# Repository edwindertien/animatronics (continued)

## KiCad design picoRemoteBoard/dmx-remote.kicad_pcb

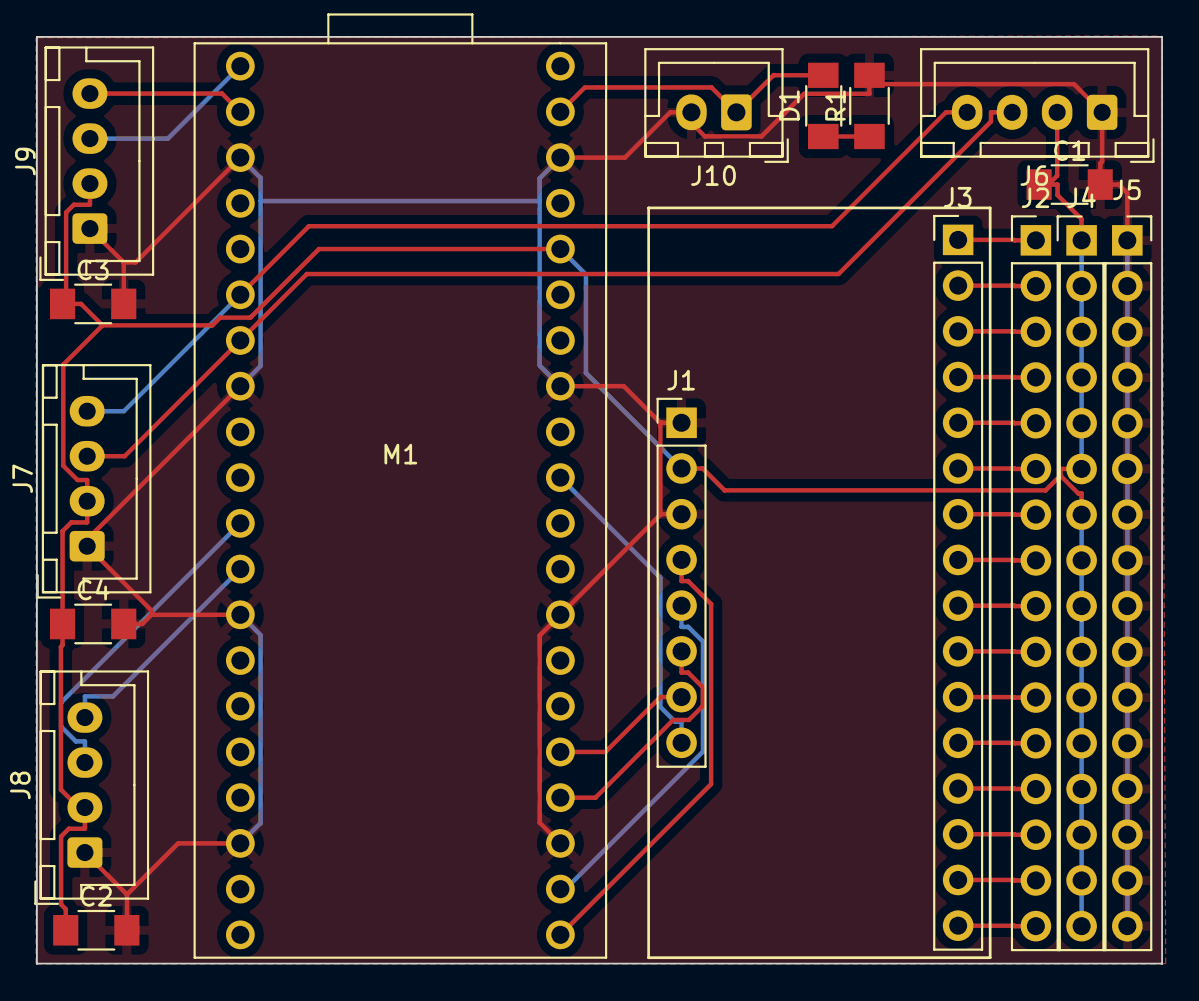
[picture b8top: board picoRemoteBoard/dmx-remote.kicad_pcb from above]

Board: 2 copper layers, 62.5 x 51.5 mm, 17 parts (0 on the bottom side), 31 nets.

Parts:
C1, C2, C3, C4: 100n; C_1206
D1: LED; LED_1206
J1: multiplexer control; PinHeader_1x08_P2.54mm_Vertical
J2: multiplexer in; PinHeader_1x16_P2.54mm_Vertical
J3: inputs; PinHeader_1x16_P2.54mm_Vertical
J4: vcc inputs; PinHeader_1x16_P2.54mm_Vertical
J5: gnd inputs; PinSocket_1x16_P2.54mm_Vertical
J6: oled; JST_XH_B4B-XH-A_1x04_P2.50mm_Vertical
J7: nunchuck; JST_XH_B4B-XH-A_1x04_P2.50mm_Vertical
J8: RF; JST_XH_B4B-XH-A_1x04_P2.50mm_Vertical
J9: DMX; JST_XH_B4B-XH-A_1x04_P2.50mm_Vertical
J10: power; JST_XH_B2B-XH-A_1x02_P2.50mm_Vertical
M1: Module_RaspberryPi_PicoW_Combined; RaspberryPi_PicoW_SocketTHT
R1: 330R; R_1206

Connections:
+3.3V: C1.1, C2.1, C3.1, C4.1, J1.2, J4.1, J4.2, J4.3, J4.4, J4.5, J4.6, J4.7, J4.8, J4.9, J4.10, J4.11, J4.12, J4.13, J4.14, J4.15, J4.16, J6.2, J7.2, J8.2, J9.2, M1.36 (3V3_OUT)
+5V: D1.2 (A), J10.1, M1.39 (VSYS)
/DMX-RxD: J9.3, M1.1 (GP0)
/DMX-TxD: J9.4, M1.2 (GP1)
/RF-RxD: J8.3, M1.11 (GP8)
/RF-TxD: J8.4, M1.12 (GP9)
/SCL: J6.3, J7.3, M1.7 (GP5)
/SDA: J6.4, J7.4, M1.6 (GP4)
GND: C1.2, C2.2, C3.2, C4.2, J1.1, J1.3, J5.1, J5.2, J5.3, J5.4, J5.5, J5.6, J5.7, J5.8, J5.9, J5.10, J5.11, J5.12, J5.13, J5.14, J5.15, J5.16, J6.1, J7.1, J8.1, J9.1, J10.2, M1.3 (GND), M1.8 (GND), M1.13 (GND), M1.18 (GND), M1.23 (GND), M1.28 (GND), M1.33 (GND), M1.38 (GND), R1.2
unnamed: D1.1 (K), R1.1
unnamed: J1.4, M1.21 (GP16)
unnamed: J1.5, M1.22 (GP17)
unnamed: J1.6, M1.24 (GP18)
unnamed: J1.7, M1.25 (GP19)
unnamed: J1.8, M1.31 (GP26)
unnamed: J2.1, J3.1
unnamed: J2.2, J3.2
unnamed: J2.3, J3.3
unnamed: J2.4, J3.4
unnamed: J2.5, J3.5
unnamed: J2.6, J3.6
unnamed: J2.7, J3.7
unnamed: J2.8, J3.8
unnamed: J2.9, J3.9
unnamed: J2.10, J3.10
unnamed: J2.11, J3.11
unnamed: J2.12, J3.12
unnamed: J2.13, J3.13
unnamed: J2.14, J3.14
unnamed: J2.15, J3.15
unnamed: J2.16, J3.16

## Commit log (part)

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2024-08-04 first commit picoControl
2024-08-09 add crossfire (8 channels)
2024-08-15 first remote sources added
2024-08-15 all basics working (RF,DMX,chuck,mux,oled)
2024-08-15 minor edit
2024-08-15 started with graphical menu
2024-08-15 added kicad files
2024-09-01 adapted for ALAN
2024-10-27 added usb host support
2024-10-27 graphic viz completed
2024-10-29 added akai midi panel lpo8
2024-11-05 adapted for klara
2024-11-07 added picoServo
2024-11-07 added boxes and other files
2024-11-07 added artnet dmx project
2024-11-07 minor changes
2024-11-08 artnetDMX shifted to two cores
2024-11-21 added box and board for artnet node
2025-01-01 sources for MIDI pico device added
2025-01-09 miniMIDIpanel
2025-01-27 merged folders for picoremote
2025-01-29 folder structure adapted and added readme.md
2025-01-29 readme.md adapted
2025-01-29 updated links
2025-01-29 re-updated links
2025-01-29 images added
2025-01-29 test with imgaes as html
2025-01-29 plaatje
2025-02-27 added DC motor to picontrol
2025-02-28 added motor.cpp class
2025-03-02 added control for 3 DC motors using elektromen drivers
2025-03-23 added crsf functionality
2025-03-24 updated CRSF code in picoremote
2025-03-30 adapted transmitter and receiver for animal-love
2025-04-02 edited transmitter and receiver for animallove.
2025-04-03 16channel version + keypad added
2025-04-06 added config.h and separate files for the picoRemote
2025-04-07 added animation class to picocontrol
2025-04-09 added action class to mega board code
2025-04-11 rework for animaltroniek - 4byte switch transmission
2025-04-13 updated controlbox design (V2)
2025-04-18 added V2.0 board for picocontrol
2025-04-21 V2 board of picoCOntrol added
2025-05-02 changed config.h to only hold defines. reworked the file-depency-include-order
2025-05-02 added lumi profile for remote
2025-05-04 added joystick channels
2025-05-18 added robotLove support
2025-05-19 added firmware and rf-link docs
2025-05-23 added pinout and values for RobotLove
2025-05-30 included battery gauge (max17048) for remote
2025-05-31 added sound tracks and samples to play
2025-06-05 recorded animation and reversed servos for animallove
2025-06-08 audio support for lumi remote
2025-06-08 documented code
2025-06-08 more documentation
2025-06-08 doc doc doc
2025-06-18 audio to core 2. added watchdog timer
2025-06-19 fixed error in mega servo control. minor edits in picoControl
2025-06-30 relay control to separate files
2025-07-03 added relay library back (check!) and updated animation
2025-07-05 checked track length
2025-07-15 added desklight, waveshare support and moved failsave to config
2025-07-27 added dynamixel library to support DXL2.0. Moved original to RS485 library. changed box file and added lid
2025-08-03 tested RS485 lib vs Dynamixel. works OK
2025-08-19 tried this version for pico2 - experimental
2025-08-19 experiment
2025-08-31 added support for CAN MCP2515 and CUBEMARS motor
2025-10-12 update EXPO animation for ANIMALLOVE
2025-10-14 bug on remote not working
2025-10-14 bracket
2025-11-07 experimental remote added
2025-11-07 edit ami code
2025-11-12 added third relay in picoControl
2025-11-23 update config.cpp system
2025-11-23 werkdag odijk
2025-12-01 code for controlboard v3.0
2025-12-01 cleaned up a bit
2025-12-07 added washing machine definitions ande code... along with a new M5 unit servo driver
2026-01-10 added desklight led driver code
2026-02-03 WIFI control added
2026-03-14 update animaltroniek en scuba
2026-03-29 removed ST3215 control to different project
2026-03-29 added vehicle_select and config.h to more files
2026-03-29 changed braketimer, tested relays for Animaltroniek
2026-04-04 select # audioplayers, scuba animation added
2026-04-19 not completely tested - csrf to core 1, audio back to 0
2026-04-19 updated version with documentation
2026-04-26 moved CRSF to core 1 (now tested and debugged for animaltroniek-vis)
2026-04-26 updated transmitter code using new protocol. THIS BREAKS THE PREVIOUS RECEIVERS!
2026-04-26 removed stale dir
2026-05-03 heavy edit of pico control and remote. AMI tested and working. Using ELRS4.0.0 and feedback
2026-05-03 ok working animallove
2026-05-03 working AMI
2026-05-03 fixed AMI blink
2026-05-03 updated animaltroniek
2026-05-04 merged picocontrol-new into picocontrol, added documentation
2026-05-04 changed doc
2026-05-18 deleted midi projects, updated readme
2026-05-20 change to animallove track
2026-05-20 updated animation track animallove
2026-05-21 changed animation
2026-05-21 run expoanimation as default
2026-05-21 edited (different) animations for expo and sequence
2026-05-21 update track
2026-05-21 again update
2026-05-21 updated documentation of picoControl
2026-05-23 updated animallove, started omniwheel washmachine
2026-05-23 update spray 0.5 sec
2026-06-02 ami sample removed rear, wasmachine added
2026-06-13 updated stofzuiger
